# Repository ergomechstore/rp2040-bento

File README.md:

# RP2040-Bento

The RP2040-bento is a breakout board for the RP2040 MCU.

The board doesn't have onboard USB port so the USB port should be designed into the carrier board.

The Fabrication files are available, these files has been tested with jlcpcb service with greate success.

This is still in development, though initial testing has been done, the design is still not in its final shape, please consider carefully before ordering from JLCPCB. You might need to do some debugging if problems arise.

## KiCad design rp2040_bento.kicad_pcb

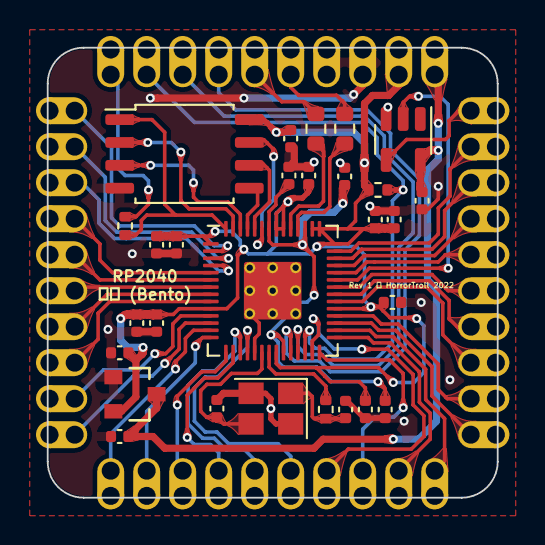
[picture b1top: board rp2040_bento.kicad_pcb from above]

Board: 2 copper layers, 25.0 x 25.0 mm, 32 parts (0 on the bottom side), 52 nets.

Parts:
C1: 10u; C_0402_1005Metric
C2, C3, C4, C5, C6, C7, C8, C9, C10, C15, C18: 100n; C_0402_1005Metric
C11, C12, C16, C17: 1u; C_0402_1005Metric
C13, C14: 22p; C_0402_1005Metric
J1, J2, J3, J4: Conn_01x10_Male; Pinouts_Castellated_Oval_01x10
R1: 10K; R_0402_1005Metric
R2, R3: 1K; R_0402_1005Metric
R6, R7: 27R; R_0603_1608Metric
RG1: XC6206P332MR; Torex-XC6206P332MR
U1: RP2040; RP2040-QFN-56
U2: W25Q128JVSIQ; SOIC-8_5.23x5.23mm_P1.27mm
U3: 74LVC1G17; SOT-23-5
Y1: 12Mhz; Crystal_SMD_3225-4Pin_3.2x2.5mm

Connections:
+1V1: C9.1, C10.1, C12.1, U1.23 (DVDD), U1.45 (VREG_VOUT), U1.50 (DVDD)
+3V3: C1.1, C2.1, C3.1, C4.1, C5.1, C6.1, C7.1, C8.1, C11.1, C15.1, C17.1, J1.2, R1.1, RG1.2 (VOUT), U1.1 (IOVDD), U1.10 (IOVDD), U1.22 (IOVDD), U1.33 (IOVDD), U1.42 (IOVDD), U1.43 (ADC_AVDD), U1.44 (VREG_VIN), U1.48 (USB_VDD), U1.49 (IOVDD), U2.8 (VCC)
+5V: C16.1, C18.1, J1.1, RG1.3 (VIN), U3.5
/DM: J1.5, R7.2
/DP: J1.6, R6.2
/~USB_BOOT: J1.10, R3.1
ARGB_3V3: U1.37 (GPIO25), U3.2
ARGB_5V: J3.10, U3.4
D+: R6.1, U1.47 (D+)
D-: R7.1, U1.46 (D-)
FLASH_SCK: U1.52 (QSPI_SCLK), U2.6 (CLK)
FLASH_SD0: U1.53 (QSPI_SD0), U2.5 (DI(IO0))
FLASH_SD1: U1.55 (QSPI_SD1), U2.2 (DO(IO1))
FLASH_SD2: U1.54 (QSPI_SD2), U2.3 (IO2)
FLASH_SD3: U1.51 (QSPI_SD3), U2.7 (IO3)
FLASH_nCS: R3.2, U1.56 (QSPI_SS_N), U2.1 (~CS)
GND: C1.2, C2.2, C3.2, C4.2, C5.2, C6.2, C7.2, C8.2, C9.2, C10.2, C11.2, C12.2, C13.2, C14.2, C15.2, C16.2, C17.2, C18.2, J1.3, J1.4, RG1.1 (VSS), U1.19 (TESTEN), U1.57 (GND), U2.4 (GND), U3.3, Y1.2, Y1.4
GPIO0: J2.1, U1.2 (GPIO0)
GPIO1: J2.2, U1.3 (GPIO1)
GPIO2: J2.3, U1.4 (GPIO2)
GPIO3: J2.4, U1.5 (GPIO3)
GPIO4: J2.5, U1.6 (GPIO4)
GPIO5: J2.6, U1.7 (GPIO5)
GPIO6: J2.7, U1.8 (GPIO6)
GPIO7: J2.8, U1.9 (GPIO7)
GPIO8: J2.9, U1.11 (GPIO8)
GPIO9: J2.10, U1.12 (GPIO9)
GPIO10: J4.1, U1.13 (GPIO10)
GPIO11: J4.2, U1.14 (GPIO11)
GPIO12: J4.3, U1.15 (GPIO12)
GPIO13: J4.4, U1.16 (GPIO13)
GPIO14: J4.5, U1.17 (GPIO14)
GPIO15: J4.6, U1.18 (GPIO15)
GPIO16: J4.7, U1.27 (GPIO16)
GPIO17: J4.8, U1.28 (GPIO17)
GPIO18: J4.9, U1.29 (GPIO18)
GPIO19: J4.10, U1.30 (GPIO19)
GPIO20: J3.1, U1.31 (GPIO20)
GPIO21: J3.2, U1.32 (GPIO21)
GPIO22: J3.3, U1.34 (GPIO22)
GPIO23: J3.4, U1.35 (GPIO23)
GPIO24: J3.5, U1.36 (GPIO24)
GPIO26: J3.6, U1.38 (GPIO26/ADC0)
GPIO27: J3.7, U1.39 (GPIO27/ADC1)
GPIO28: J3.8, U1.40 (GPIO28/ADC2)
GPIO29: J3.9, U1.41 (GPIO29/ADC3)
unnamed: C14.1, R2.2, Y1.1
SWCLK: J1.7, U1.24 (SWCLK)
SWDIO: J1.8, U1.25 (SWDIO)
XTAL1: C13.1, U1.20 (XTAL_IN), Y1.3
XTAL2: R2.1, U1.21 (XTAL_OUT)
~NRST: J1.9, R1.2, U1.26 (~RUN)

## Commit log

2022-10-24 add pictures
2022-10-24 fix images
2022-10-24 Create LICENSE
2022-10-28 adding pictures

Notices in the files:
rp2040_bento.kicad_pcb:
Copyright © 2022 HorrorTroll
MIT License
